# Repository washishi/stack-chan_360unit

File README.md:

# stack-chan_360unit
Rotation unit for Takao's SCS0009 version stack chan

## 説明
-  タカヲ([@mongonta555](https://x.com/mongonta555))さんの [SCS0009サーボ専用 ｽﾀｯｸﾁｬﾝ](https://raspberrypi.mongonta.com/about-products-stackchan-m5gobottom-version/) を回転させてもUSBケーブルが邪魔にならないようにするユニットです
- [【SCS0009専用】ｽﾀｯｸﾁｬﾝ タカオ版 ケースセット](https://mongonta.booth.pm/items/5186064)に後付けできます
-  M5Coreへの電源供給は Groveポート経由、USBコネクタ経由(外部/内部)いずれかで行うことができます  
-  USBコネクタ(外部/内部)を利用した場合は電源の供給だけでなくデータ通信も行うことができます
  
<br>
<br>

## BOOTHで頒布するセットの説明
BOOTHで頒布する[タカヲ版 SCS0009 ｽﾀｯｸﾁｬﾝ用 360ユニット セット](https://washishi.booth.pm/items/7204147)は下記のセットとなっています
<br>
1. 360ユニット 基板A  
   電源等を伝達するための基板です  
   GroveおよびUSB接続用のコネクタ、電源供給先切替用のスイッチが付いています
2. 360ユニット 基板B  
   電源元のUSBからの受電部です ここにACアダプタ等を接続します(同時に他の場所等の2か所から給電しないでください)  
   USB Type-C コネクタ部分は スーザン＠子育てエンジニア([@suzan_works](https://x.com/suzan_works)
)さんの  
[プリント基板製USB-Cコネクタ](https://suzan-works.booth.pm/items/6574802)の[設計データ](https://github.com/suzan-works/USB-C_PCB_Receptacle)を利用させてもらっています  
USB Type-Cコネクタを刺すため厚さは0.8mmです
3. サーボ用スペーサー
   360Unitの接点の入る厚みを確保するために足側のサーボとブラケットの間に挟みます
4. USB(外部)用ケーブル  
   M5CoreのUSB Type-C 端子と接続する場合に利用するケーブルです  
   LLMモジュールを付けている場合はそちらのUSB Type-C端子に接続することもできます  
   結線はCore内部の表記と同じで下記となります  
    1.+5V(赤)  
    2.GND(黒)  
    3.D-(DM) (黄)  
    4.D+(DP) (緑)  
5. USB(内部)用ケーブル  
   Core2 や CoreS3※,S3SE,S3Lite 等の内部にある1.25mmピッチのUSBコネクタと接続する場合に利用するケーブルです  
   コネクタ同士の結線はストレート(同じピン同士が接続)です  
   ※CoreS3の初期ロット？にはこのコネクタが実装されていない様です
6. Groveケーブル 10cm  
   GroveコネクタからM5Coreに給電する際に360ユニットとCoreのGrove端子を接続するケーブルです   
7. 1.25mmピッチコネクタ  
   CoreS3の初期ロット？では内部USBコネクタが未実装の様なので自分で実装する場合の為に1つ添付しています・・・がCoreS3の分解は難易度が高い為自信がない場合は行わない方がいいです(分解方法についてもここでは解説しません)
## 組み立て方
1. 利用する工具等
   - ドライバ　または 六角レンチ  
     ｽﾀｯｸﾁｬﾝの足(サーボホーン)とサーボの固定ネジの取り外し/取り付けに利用します  
     利用しているネジに合ったものを準備してください
   - やすり  
     サーボホーンがガタつくときや360ユニット基板Bがはめにくい場合に使う場合があります(100均のダイヤモンドやすりでかまいません)
   - ニッパー  
     サーボ用スペーサーを切って取り付ける場合は利用します
   - ピンセット  
     コネクタを刺す際にあると便利です

2. すでにｽﾀｯｸﾁｬﾝが組みあがっている場合は正面を向いた状態(サーボが中点)で停止します  
   新規で組み立てる場合も位置を動かしてしまっている場合は中点に合わせてください
3. ｽﾀｯｸﾁｬﾝの足(サーボホーン)のネジを外して取り外します  
   サーボホーンを乗せた状態でガタつかず水平になることを確認します  
   ガタつく場合はサーボホーンの側面(下記写真の赤色部分)を少しやすりで削って足の固定部分と干渉しないようにします  
     
4. 360ユニット 基板B を写真の向きで足にはめます  
   窪みに合わせてサーボホーンに当たるまで押し込みます  
   はめにくい場合は基板の側面をやすりで少し削ってください  
   
5. サーボの固定ネジ(2本)を取り外しサーボとブラケットの間にスペーサーを入れて再度固定ネジで止めます  
   組みあがった状態だとサーボのケーブルを一度外す必要があり面倒なので写真のようにスペーサーをニッパーでカットしてしまってもいいです  
 <br>
 <br>

6. 360ユニット 基板Aを写真の向きでサーボにはめてからｽﾀｯｸﾁｬﾝの足を再度取り付けます  
<br>
※足をねじ止めする前に次の「7.配線」を行った方が配線がしやすいかもしれません

7. 配線  
   コネクタ同士の配線を行います

   以下の接続ができます  
   - USB(外部)給電 (CoreのUSBコネクタから給電)
   - USB(内部)給電 (Core2,S3系(※)の内部USBコネクタから給電) 
   - Grove給電 (CoreやGoBottomのGroveポートから給電)  
    
    接続方法  
      |給電|接続方法|スイッチ|データ  通信|  
    |:-|:--|:--|:-:| 
    |USB<br>(外部)|「To M5 USB」と M5Core のUSBコネクタを「USB(外部)用ケーブル」で繋ぎます|USB側|可|  
    |USB<br>(内部)|「To M5 USB」と M5Core2,S3系(※)の内部USBコネクタを「USB(内部)用ケーブル」で繋ぎます|USB側|可|  
    |Grove|M5CoreやGOBottomのGroveポートを「GROVEケーブル」で「To M5」のGroveポート(横)と繋ぎます、TakaoBASEは「To TakaoBase」のGroveポート(縦)に繋ぎます|Grove側|不可|  

   - USBとGroveの両方の配線を行っても電源の供給先はスイッチで切替となるので問題ありません  
   - ※CoreS3の初期ロット？では内部USBコネクタが実装されていません(使う場合はCoreS3を分解して自分で実装する必要があります)  
  
USB(内部)コネクタ(左写真)、USB(内部)コネクタ利用でLLMモジュールを付ける場合はLLMモジュールの基板下に少し隙間があるので一度基板を止めているネジを外して通してください(右写真)  

配線の完了で作業は完了です  

## 使い方
ｽﾀｯｸﾁｬﾝの足の後ろに飛び出しているUSB Type-CコネクタにACアダプタやPCを接続して給電します  
CoreとUSBケーブル(外部/内部)で接続している場合はPCと繋ぐとプログラム書き込み等のデータ通信も行えます  

## 基板制作データ等
<br>
<br>

本リポジトリ schematics の配下に kicad (v9)で作成した回路図、基板データ一式があります  
また schematics/production 配下には基板発注に利用するガーバデータのzipファイルもあります

## BOM(部品リスト)
|名称|仕様|メーカー|個数|備考|備考購入先|  
|:--|:--|:-:|:-:|:--|:--|  
|基板|stack-chan 360Unit A基板|-|1||[JLCPCB](https://jlcpcb.com/JPV)へ発注|
|基板|stack-chan 360Unit B基板|-|1|厚さ0.8mm|[JLCPCB](https://jlcpcb.com/JPV)へ発注|
|チップ抵抗|5.1KΩ 1608サイズ|-|2||[秋月電子](https://akizukidenshi.com/catalog/g/g130338/)100個セット|
|チップ積層セラミックコンデンサ|100uF 10V 3216サイズ|-|1||[秋月電子](https://akizukidenshi.com/catalog/g/g115633/)10個セット|
|スイッチ|2.5mmピッチ SPDT サイド型|-|1||[秋月電子](https://akizukidenshi.com/catalog/g/g115370/)|
|Groveコネクタ|HY2.0-4P ストレート|-|1||[秋月電子](https://akizukidenshi.com/catalog/g/g131074/)10個セット|
|Groveコネクタ|HY2.0-4P L形|-|1||[秋月電子](https://akizukidenshi.com/catalog/g/g112634/)10個セット|
|1.25mmコネクタ ケーブルセット|4P 10cm 片側のみコネクタ圧着|-|2|ケーブル1<br> コネクタ2|[Aliexpress](https://ja.aliexpress.com/item/1005006003135511.html)10ペア セット||
|1.25mmコネクタ ケーブル|4P ストレート 100mm<br>両側コネクタ|-|1||[Aliexpress](https://ja.aliexpress.com/item/1005005898168919.html)10個セット||
|USB Type-Cコネクタ|MX-12とあるもの|-|1||[Aliexpress](https://ja.aliexpress.com/item/1005007581371610.html)||
|バッテリー端子|smd 1.27mmピッチ 4P|-|2|ばね接点|[Aliexpress](https://ja.aliexpress.com/item/1005005302903409.html)5個セット||
|シリコンチューブ|内径2mm外形3mm|-|6cmほど|USB(外部)ケーブルに被せてます|[Aliexpress](https://ja.aliexpress.com/item/1005001499980646.html)1m||

## 3Dモデル等
3D_Model 配下に 下記の利用した3Dモデルデータ(STEP,STL形式)があります
 - サーボスペーサ
 - USB Type-C コネクタケース 上部
 - USB Type-C コネクタケース 下部

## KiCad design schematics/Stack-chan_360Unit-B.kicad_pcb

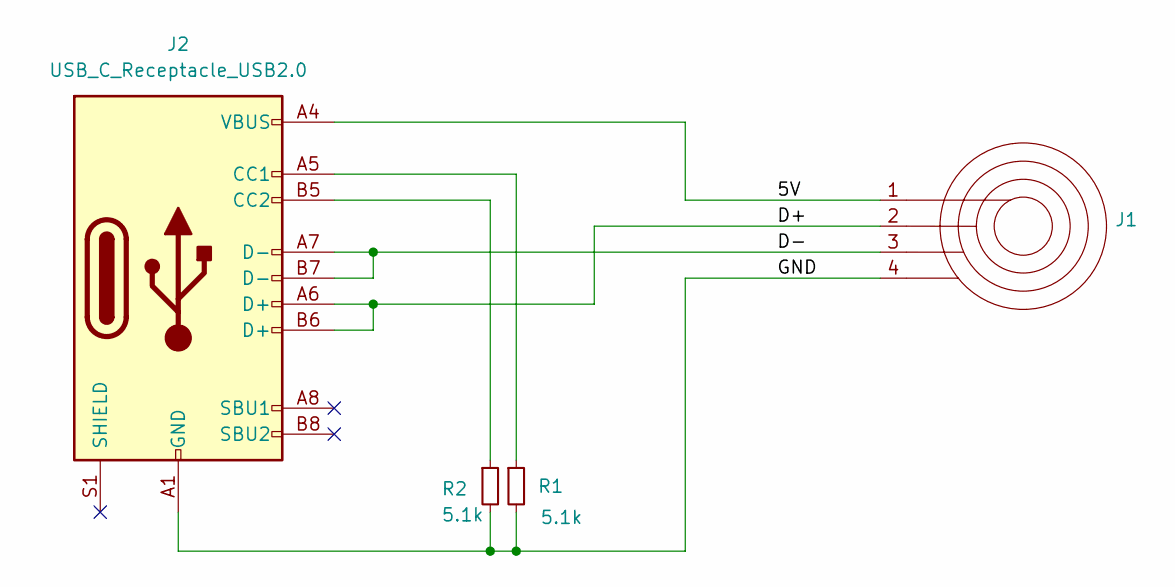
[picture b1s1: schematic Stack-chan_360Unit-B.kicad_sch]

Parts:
J1: RingTerminal
J2: USB_C_Receptacle_USB2.0; USB-C_PCBPLUG
R1, R2: 5.1k; R_0603_1608Metric

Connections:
/5V: J1.1, J2.A4 (VBUS), J2.A9 (VBUS), J2.B4 (VBUS), J2.B9 (VBUS)
/D+: J1.2, J2.A6 (D+), J2.B6 (D+)
/D-: J1.3, J2.A7 (D-), J2.B7 (D-)
/GND: J1.4, J2.A1 (GND), J2.A12 (GND), J2.B1 (GND), J2.B12 (GND), R1.2, R2.2
unnamed: J2.A5 (CC1), R1.1
unnamed: J2.B5 (CC2), R2.1

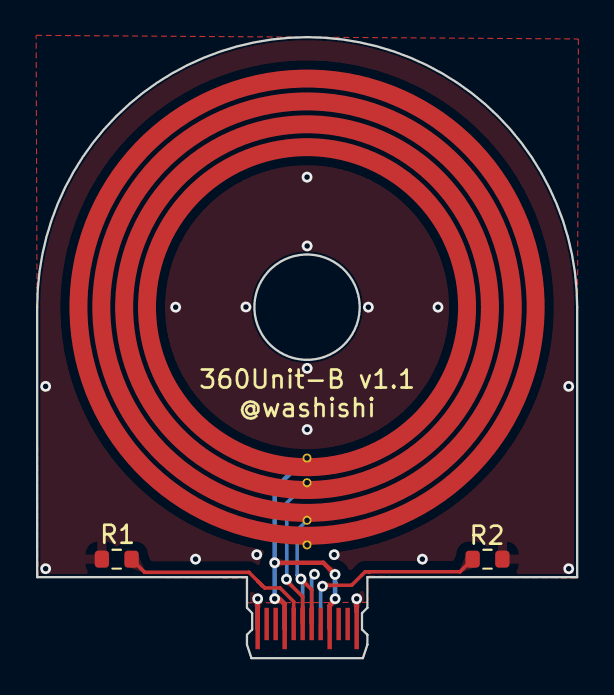
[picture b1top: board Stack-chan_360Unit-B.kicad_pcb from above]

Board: 2 copper layers, 30.0 x 34.5 mm, 4 parts (0 on the bottom side), 6 nets.

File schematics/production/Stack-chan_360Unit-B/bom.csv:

Designator,Footprint,Quantity,Value,LCSC Part #
J1,RingTerminal,1,~,
J2,USB-C_PCBPLUG,1,USB_C_Receptacle_USB2.0,
"R1, R2",0603,2,5.1k,

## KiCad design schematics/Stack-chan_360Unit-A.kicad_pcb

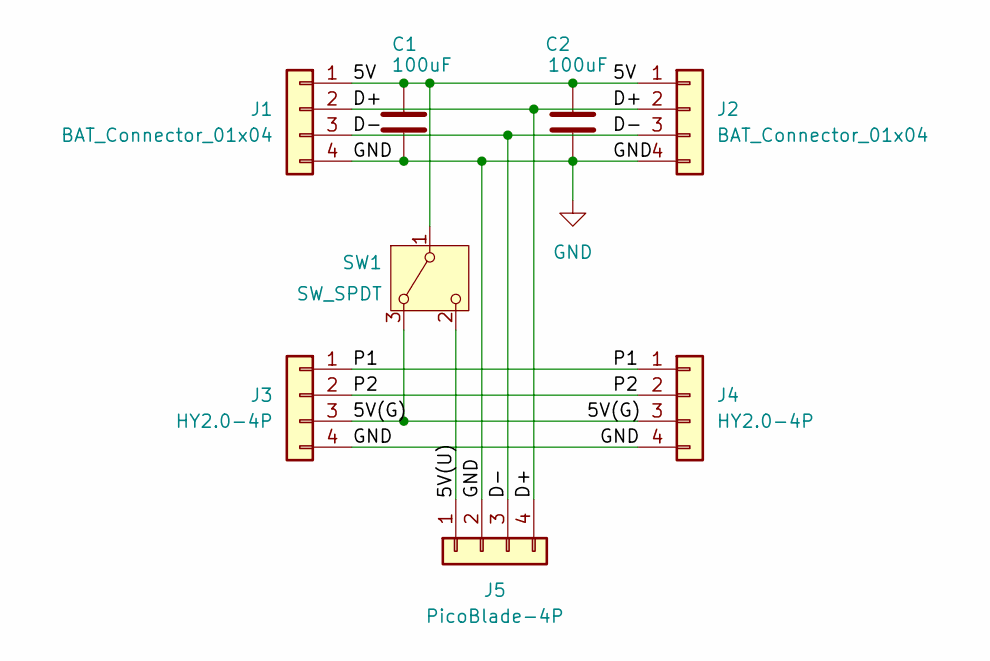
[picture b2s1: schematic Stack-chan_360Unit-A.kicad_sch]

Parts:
C1, C2: 100uF; C_1206_3216Metric_Pad1.33x1.80mm_HandSolder
J1, J2: BAT_Connector_01x04; BatteryConector_1.27mm_4P
J3: HY2.0-4P; NS-Tech_Grove_1x04_P2mm_Vertical
J4: HY2.0-4P; CON_GROVE_H
J5: PicoBlade-4P; Molex_PicoBlade_53047-0410_1x04_P1.25mm_Vertical
SW1: SW_SPDT; SW_Slide-03_Wuerth-WS-SLTV_9x3.5x3.5_P2.54mm

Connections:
/5V: C1.1, C2.1, J1.1, J2.1, SW1.1 (B)
/5V(G): J3.3, J4.3, SW1.3 (A)
/5V(U): J5.1, SW1.2 (C)
/D+: J1.2, J2.2, J5.4
/D-: J1.3, J2.3, J5.3
/P1: J3.1, J4.1
/P2: J3.2, J4.2
GND: C1.2, C2.2, J1.4, J2.4, J3.4, J4.4, J5.2

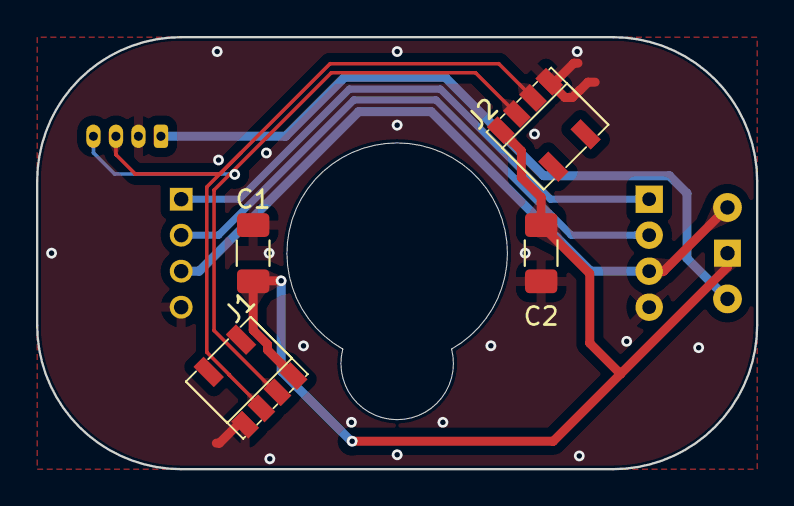
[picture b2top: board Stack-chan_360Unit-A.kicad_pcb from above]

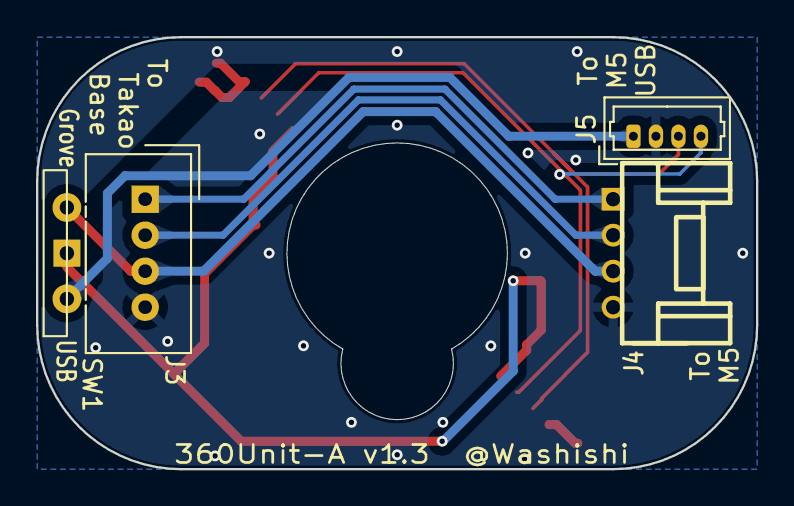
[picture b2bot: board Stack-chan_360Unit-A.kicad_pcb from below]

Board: 2 copper layers, 40.0 x 24.0 mm, 8 parts (4 on the bottom side), 8 nets.

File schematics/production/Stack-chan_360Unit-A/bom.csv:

Designator,Footprint,Quantity,Value,LCSC Part #
"C1, C2",1206,2,100uF,
"J1, J2",BatteryConector_1.27mm_4P,2,BAT_Connector_01x04,
J3,NS-Tech_Grove_1x04_P2mm_Vertical,1,HY2.0-4P,
J4,CON_GROVE_H,1,HY2.0-4P,
J5,Molex_PicoBlade_53047-0410_1x04_P1.25mm_Vertical,1,PicoBlade-4P,
SW1,SW_Slide-03_Wuerth-WS-SLTV_9x3.5x3.5_P2.54mm,1,SW_SPDT,
